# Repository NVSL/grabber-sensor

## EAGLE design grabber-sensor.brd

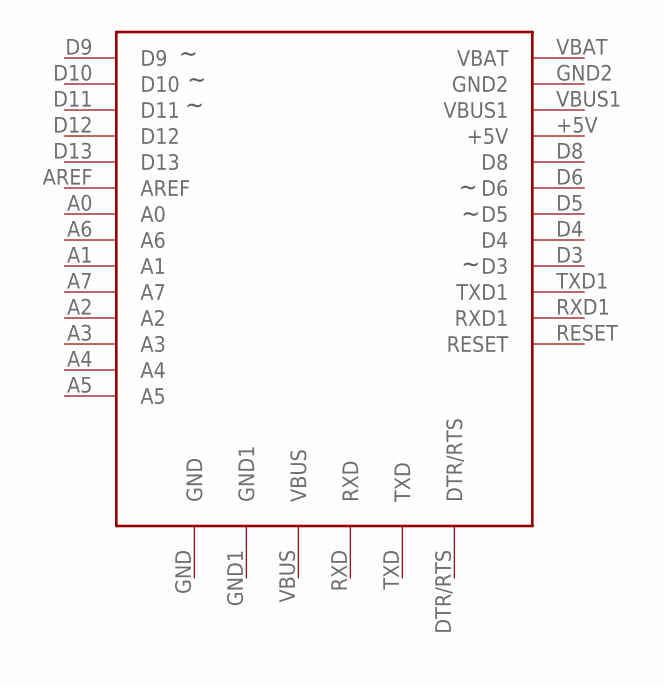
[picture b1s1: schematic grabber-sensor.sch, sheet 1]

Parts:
U1_0_BRAIN: ADAFRUIT-PRO-TRINKET-5V-BOB; ADAFRUIT-PRO-TRINKET-5V

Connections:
+5V_0_BRAIN: U1_0_BRAIN.+5V; also elsewhere on the board
A0_0_BRAIN: U1_0_BRAIN.A0; also elsewhere on the board
A1_0_BRAIN: U1_0_BRAIN.A1; also elsewhere on the board
A2_0_BRAIN: U1_0_BRAIN.A2; also elsewhere on the board
A3_0_BRAIN: U1_0_BRAIN.A3
A4_0_BRAIN: U1_0_BRAIN.A4
A5_0_BRAIN: U1_0_BRAIN.A5
A6_0_BRAIN: U1_0_BRAIN.A6
A7_0_BRAIN: U1_0_BRAIN.A7
AREF_0_BRAIN: U1_0_BRAIN.AREF
D3_0_BRAIN: U1_0_BRAIN.D3; also elsewhere on the board
D4_0_BRAIN: U1_0_BRAIN.D4; also elsewhere on the board
D5_0_BRAIN: U1_0_BRAIN.D5; also elsewhere on the board
D6_0_BRAIN: U1_0_BRAIN.D6; also elsewhere on the board
D8_0_BRAIN: U1_0_BRAIN.D8; also elsewhere on the board
D9_0_BRAIN: U1_0_BRAIN.D9; also elsewhere on the board
D10_0_BRAIN: U1_0_BRAIN.D10; also elsewhere on the board
D11_0_BRAIN: U1_0_BRAIN.D11; also elsewhere on the board
D12_0_BRAIN: U1_0_BRAIN.D12; also elsewhere on the board
D13_0_BRAIN: U1_0_BRAIN.D13; also elsewhere on the board
DTR/RTS_0_BRAIN: U1_0_BRAIN.DTR/RTS
GND_0_BRAIN: U1_0_BRAIN.GND, U1_0_BRAIN.GND1, U1_0_BRAIN.GND2; also elsewhere on the board
POS_1_BATTERY: U1_0_BRAIN.VBAT; also elsewhere on the board
RESET_0_BRAIN: U1_0_BRAIN.RESET
RXD1_0_BRAIN: U1_0_BRAIN.RXD1
RXD_0_BRAIN: U1_0_BRAIN.RXD
TXD1_0_BRAIN: U1_0_BRAIN.TXD1
TXD_0_BRAIN: U1_0_BRAIN.TXD
VBUS1_0_BRAIN: U1_0_BRAIN.VBUS1
VBUS_0_BRAIN: U1_0_BRAIN.VBUS

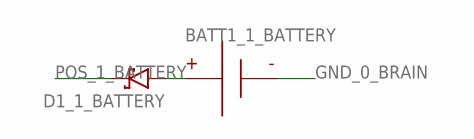
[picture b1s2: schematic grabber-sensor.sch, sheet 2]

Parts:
BATT1_1_BATTERY: BATTERY-9V-VERTICAL; BATTERY_9V_KEYSTONE_968
D1_1_BATTERY: RESOLVED-DIODE-SCHOTTKY_TH-DO-41-AND-DO-204AL; DIOAD1125W78L520D270_HS; MPN 1N5817

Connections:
GND_0_BRAIN: BATT1_1_BATTERY.N; also elsewhere on the board
unnamed: BATT1_1_BATTERY.P, D1_1_BATTERY.A
POS_1_BATTERY: D1_1_BATTERY.C; also elsewhere on the board

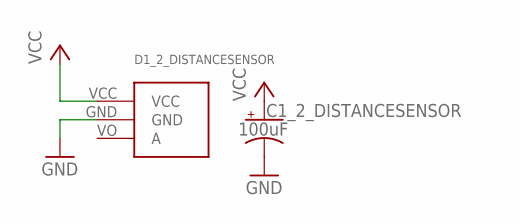
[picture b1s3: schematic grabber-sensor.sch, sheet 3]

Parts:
C1_2_DISTANCESENSOR: 100uF; CAPPRD250W80D630H1220P; MPN ECA-1EM101
D1_2_DISTANCESENSOR: ANALOG_DISTANCE_SENSOR-GLUE; ANALOG_DISTANCE_SENSOR_GLUE_MOUNT

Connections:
+5V_0_BRAIN: C1_2_DISTANCESENSOR.1 (+), D1_2_DISTANCESENSOR.VCC; also elsewhere on the board
A2_0_BRAIN: D1_2_DISTANCESENSOR.VO (A); also elsewhere on the board
GND_0_BRAIN: C1_2_DISTANCESENSOR.2 (-), D1_2_DISTANCESENSOR.GND; also elsewhere on the board

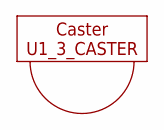
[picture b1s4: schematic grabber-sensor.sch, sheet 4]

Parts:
U1_3_CASTER: CASTERADAFRUIT-3/4IN; ADAFRUIT-3/4IN-CASTER

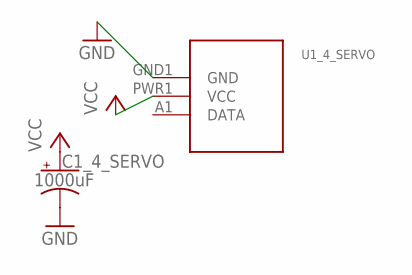
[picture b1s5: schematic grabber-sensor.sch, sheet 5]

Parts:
C1_4_SERVO: 1000uF; CAPPRD500W80D1000H2200P; MPN ECA-1EM102
U1_4_SERVO: SERVO-MICRO_SIDE_GLUE; SERVO_MICRO_SIDE_GLUE

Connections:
D3_0_BRAIN: U1_4_SERVO.A1 (DATA); also elsewhere on the board
GND_0_BRAIN: C1_4_SERVO.2 (-), U1_4_SERVO.GND1 (GND); also elsewhere on the board
POS_1_BATTERY: C1_4_SERVO.1 (+), U1_4_SERVO.PWR1 (VCC); also elsewhere on the board

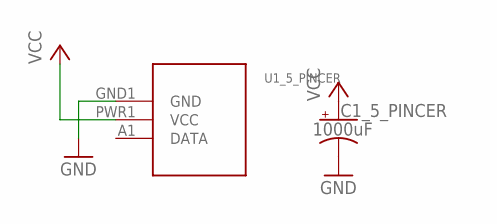
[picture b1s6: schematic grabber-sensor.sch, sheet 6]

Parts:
C1_5_PINCER: 1000uF; CAPPRD500W80D1000H2200P; MPN ECA-1EM102
U1_5_PINCER: MICRO_GRIPPER

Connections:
D5_0_BRAIN: U1_5_PINCER.A1 (DATA); also elsewhere on the board
GND_0_BRAIN: C1_5_PINCER.2 (-), U1_5_PINCER.GND1 (GND); also elsewhere on the board
POS_1_BATTERY: C1_5_PINCER.1 (+), U1_5_PINCER.PWR1 (VCC); also elsewhere on the board

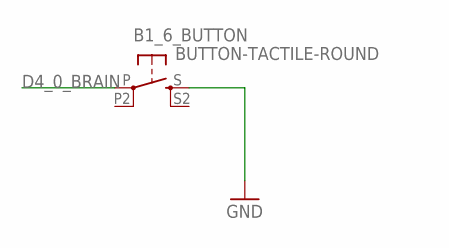
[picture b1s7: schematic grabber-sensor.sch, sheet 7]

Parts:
B1_6_BUTTON: BUTTON-TACTILE-ROUND; BUTTON-TACTILE-ROUND-ADAFRUIT1009

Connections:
D4_0_BRAIN: B1_6_BUTTON.P; also elsewhere on the board
GND_0_BRAIN: B1_6_BUTTON.S; also elsewhere on the board

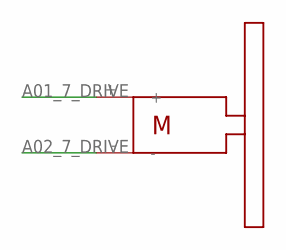
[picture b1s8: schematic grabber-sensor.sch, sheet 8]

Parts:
R_7_DRIVE: SOLARBOTICS_GM2SPARKFUN_HOBBY; SPARKFUN_HOBBY_MOTOR

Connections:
A01_7_DRIVE: R_7_DRIVE.+; also elsewhere on the board
A02_7_DRIVE: R_7_DRIVE.-; also elsewhere on the board

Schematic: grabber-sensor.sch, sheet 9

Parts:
L_7_DRIVE: SOLARBOTICS_GM2_LEFTSPARKFUN_HOBBY; SPARKFUN_HOBBY_MOTOR_LEFT

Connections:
B01_7_DRIVE: L_7_DRIVE.+; also elsewhere on the board
B02_7_DRIVE: L_7_DRIVE.-; also elsewhere on the board

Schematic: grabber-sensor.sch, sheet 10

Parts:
C1_7_DRIVE: 3300uF; CAPPRD750W80D1600H2200P; MPN ECA-1EM332
DRVR_7_DRIVE: SPARKFUN_DUAL_MOTOR_DRIVER-BOB; SPARKFUN_DUAL_MOTOR_DRIVER

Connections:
+5V_0_BRAIN: DRVR_7_DRIVE.VCC; also elsewhere on the board
A01_7_DRIVE: DRVR_7_DRIVE.A01; also elsewhere on the board
A02_7_DRIVE: DRVR_7_DRIVE.A02; also elsewhere on the board
B01_7_DRIVE: DRVR_7_DRIVE.B01; also elsewhere on the board
B02_7_DRIVE: DRVR_7_DRIVE.B02; also elsewhere on the board
D6_0_BRAIN: DRVR_7_DRIVE.PWMA; also elsewhere on the board
D8_0_BRAIN: DRVR_7_DRIVE.STBY; also elsewhere on the board
D9_0_BRAIN: DRVR_7_DRIVE.PWMB; also elsewhere on the board
D10_0_BRAIN: DRVR_7_DRIVE.AIN1; also elsewhere on the board
D11_0_BRAIN: DRVR_7_DRIVE.AIN2; also elsewhere on the board
D12_0_BRAIN: DRVR_7_DRIVE.BIN1; also elsewhere on the board
D13_0_BRAIN: DRVR_7_DRIVE.BIN2; also elsewhere on the board
GND_0_BRAIN: C1_7_DRIVE.2 (-), DRVR_7_DRIVE.GND, DRVR_7_DRIVE.GND1, DRVR_7_DRIVE.GND2; also elsewhere on the board
POS_1_BATTERY: C1_7_DRIVE.1 (+), DRVR_7_DRIVE.VM; also elsewhere on the board

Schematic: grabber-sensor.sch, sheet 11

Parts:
U$2_8_BUMP: BUMP_SWITCH-MEDIUM-LEFT; BUMP_SWITCH_OMRON_D2FLA

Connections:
A0_0_BRAIN: U$2_8_BUMP.A; also elsewhere on the board
GND_0_BRAIN: U$2_8_BUMP.B; also elsewhere on the board

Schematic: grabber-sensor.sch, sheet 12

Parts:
U$2_9_BUMP_2: BUMP_SWITCH-MEDIUM-RIGHT; BUMP_SWITCH_OMRON_D2FLA1

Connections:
A1_0_BRAIN: U$2_9_BUMP_2.A; also elsewhere on the board
GND_0_BRAIN: U$2_9_BUMP_2.B; also elsewhere on the board

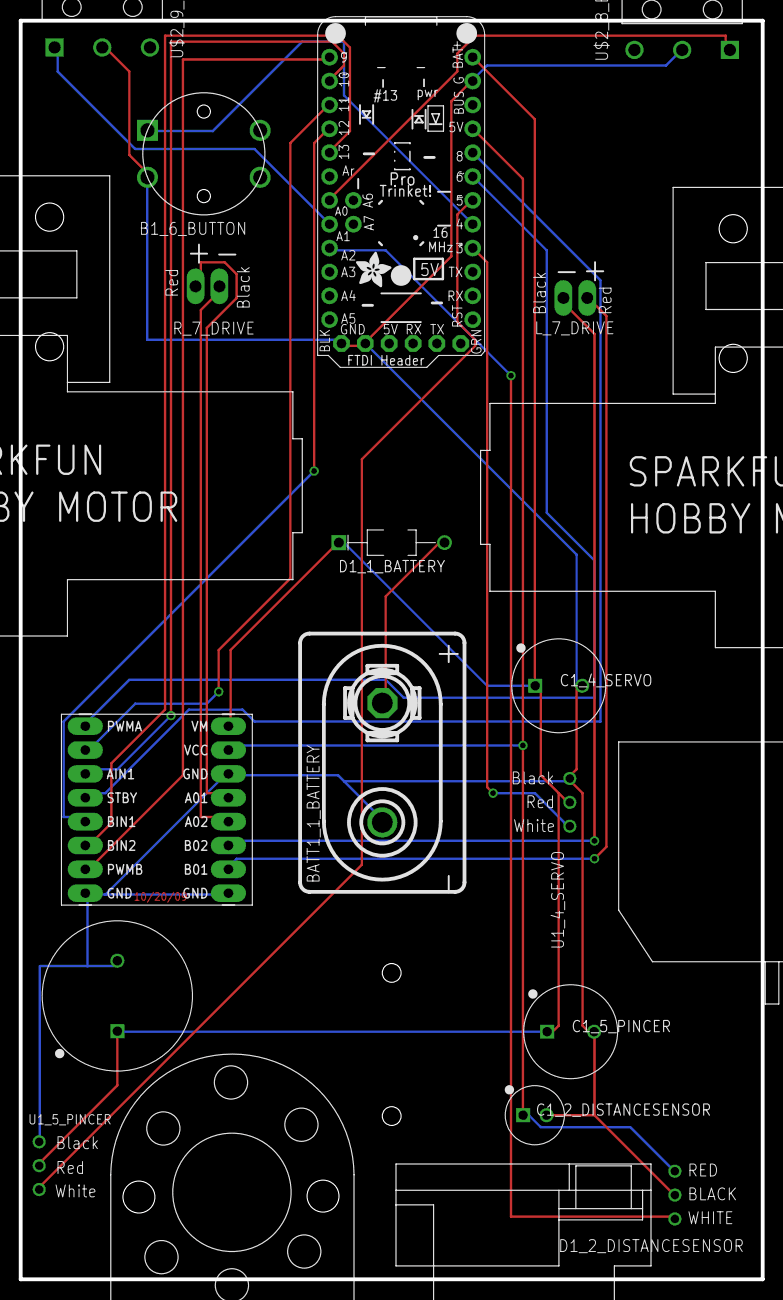
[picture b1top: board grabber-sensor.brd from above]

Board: 2 copper layers, 79.0 x 134.0 mm, 17 parts (0 on the bottom side), 21 nets.

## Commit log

2016-03-16 Robot 2 for robot parade class
2016-04-26 Added starter/test code
2016-04-28 Updated Starter code to use GadgetManager
2016-04-29 state machine example
